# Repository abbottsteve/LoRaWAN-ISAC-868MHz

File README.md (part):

# 868 MHz LoRaWAN ISAC Surface-Permittivity Sensor Node (`Rev E.5`)

[-0A66C2?style=flat-square)](#1-motivation-status--system-specifications)

[-2E7D32?style=flat-square)](docs/firmware_and_pinmap.md)

An open-hardware Integrated Sensing and Communications (ISAC) sensor node operating in the European 863–870 MHz (EU868) band [6]. Rather than pairing an auxiliary microwave resonator with a separate telemetry radio, the board shares a single Inverted-F + Interdigital Evanescent-Field Antenna (`AE1`) and a single `STM32WLE5JC` / `SX1262` System-in-Package (`RAK3172LP-SIP-8-SM-NI`) across a low-loss (-0.80 dB) asymmetric return-loss bridge to measure near-field surface permittivity through a 0.80 mm radome and transmit Class A LoRaWAN uplinks over the same physical aperture.

| Front-Left Ray-Traced PCBA (90 × 40 mm) | Rear-Right RF Bridge & Sensing Aperture (`AE1`) |
| :---: | :---: |
|  |  |

### Documentation Navigation

| Document | Technical Scope |
| :--- | :--- |
| [**System Design Summary (6-Page PDF)**](docs/ISAC_868MHz_System_Design_and_Operation_Summary.pdf) | Printable A4 technical datasheet covering architecture, analytical signal model, benchmarks, CAD & references |
| [**RF Design, EM Solvers & Limitations**](docs/rf_design_and_simulation.md) | 2D-FVM CPWG cross-section, 2,000-trial bridge Monte-Carlo, 3D-FDTD plots, sensing boundary conditions & `Rev F.0` roadmap |
| [**Firmware, `U1` Pin Map & `FPort 10` Payload**](docs/firmware_and_pinmap.md) | Freestanding C11 execution flow, silicon errata, `RAK3172LP-SiP` LGA-73 pinout + overlay & 10-byte ChirpStack/TTN decoder |
| [**Turnkey BOM, Test Points & Enclosure**](docs/bom_and_enclosure.md) | Complete 46-line BOM, `TP1..TP5` probe map, self-draining ASA/PETG Option A/B blueprints & SWD provisioning CLI |
| [**Power Budget**](docs/power_budget.md) · [**Loaded Link Budget**](docs/rf_link_budget.md) | Split-rail LDO/switch current analysis (`STOP2` 2.85–3.25 µA) & wet-radome SF7/SF9/SF12 link-margin recovery |
| [**CST Studio Suite 3D Package**](cst_studio/README.md) | Parameterized SIMULIA CST Microwave Studio (`FIT` / curved `FEM`), Debye dispersion & Design Studio co-simulation |
| [**Pilot Bring-Up Checklist**](docs/bringup_report.md) · [**Open Items**](docs/OPEN_ITEMS.md) | First-article VNA correlation, 5–10 board pilot verification procedure & ETSI pre-compliance tracker |

---

## 1. Motivation, Status & System Specifications

Detecting glaze ice, water films, or hydrocarbon spills on remote outdoor assets—bridge decks, wind-turbine blades, roadways, and utility enclosures—typically forces a trade-off between optical/ultrasonic fouling and the cost/power overhead of standalone radar sensors. At UHF, the capacitive open end of a planar antenna exhibits strong resonant sensitivity to superstrate permittivity across a thin dielectric wall [1, 3, 4]. Inserting a -0.80 dB asymmetric return-loss bridge ahead of an interdigital-tip Inverted-F antenna lets the LoRa transceiver probe three brief +4.0 dBm CW tones across EU868 to classify surface loading before transmitting telemetry over LoRaWAN.

> **Hardware Status (`Rev E.5` — Pilot Batch in Fabrication):** Schematic, 2-layer PCB, 3D-FDTD and CST Studio models, freestanding C11 firmware, and the single-sided SMT archive ([`fab/ISAC_868_RevE5_PCBWay_Turnkey.zip`](fab/ISAC_868_RevE5_PCBWay_Turnkey.zip)) are frozen at `Rev E.5`. A 5–10 unit pilot batch is currently in turnkey assembly; all RF, sensitivity, and current figures reported here are simulation- and datasheet-derived predictions awaiting physical VNA and chamber correlation ([`docs/OPEN_ITEMS.md`](docs/OPEN_ITEMS.md)).

| Subsystem | `Rev E.5` Specification | Reference / Gate |
| :--- | :--- | :--- |
| **PCB & Finish** | 90.0 × 40.0 × 1.60 mm 2-layer FR-4 (1.51 mm core, $\varepsilon_r = 4.4 \pm 0.2$, 1 oz Cu), IPC-4552 ENIG, bare-ENIG `AE1` window, 0.10 mm top stencil | [`tools/check_dfm.py`](tools/check_dfm.py) |
| **Assembly Counts** | `92` footprints = `67` populated top SMD (`0` THT) + `10` DNP + `15` `BOARD_ONLY`; `131` tented 0.60/0.30 mm vias; 0 DRC / 0 ERC | [`docs/bom_and_enclosure.md`](docs/bom_and_enclosure.md) |
| **Radio / MCU (`U1`)** | `RAK3172LP-SIP-8-SM-NI` (`STM32WLE5JC` + `SX1262` `RFO_LP`, 3.0 V `DIO3` TCXO `0x06`, 15 µH wirewound SMPS); 15,948 B Flash / 408 B RAM | [`docs/firmware_and_pinmap.md`](docs/firmware_and_pinmap.md) |
| **CPWG & Bridge** | 51.90 Ω CPWG ($W = 1.08\text{ mm}, S = 0.28\text{ mm}$); `R1` = 8.2 Ω (`RT0402BRD078R2L`) asymmetric bridge ($C_{\text{par}} = 0.1305\text{ pF}$, IL = -0.802 dB, 50 Ω directivity = 24.81 dB) | [`docs/rf_design_and_simulation.md`](docs/rf_design_and_simulation.md) |
| **Detector (`U2`)** | Analog Devices `LT5538IDD#TRPBF` (19.0 mV/dB), TX-off Listen-Before-Sense blanking ($\le 320\text{ mV}$) & $\le 39.5\text{ mV}$ unpowered swing at +14 dBm TX | [`docs/rf_link_budget.md`](docs/rf_link_budget.md) |
| **Filter & `AE1`** | 3rd-order elliptic Pi-LPF ($2f_0 \ge 37.2\text{ dB}$, $3f_0 \ge 60.1\text{ dB}$); `AE1` bonded via 25 µm 3M 467MP to 0.80 mm ASA/PETG ($f_0 = 869.0\text{ MHz}$, $\eta_{\text{tot}} = 45.5$%, 43.73 MHz/RIU, 17.60 dB `P01` ice contrast) | [`rf/ifa_enclosure_mom.py`](rf/ifa_enclosure_mom.py) |
| **Power & Enclosure** | 1S LiPo or 3.6 V Li-SOCl<sub>2</sub> $\to$ `AO3401A` + 25 nA LDO (`U3`) + `VBAT`-gated `Q1` (2.85–3.25 µA `STOP2`); 95.7 × 45.7 × 16.1 mm open-East O-ring housing | [`docs/power_budget.md`](docs/power_budget.md) |

---

## 2. Operating Principle & Analytical Reflectometer Model

```mermaid
flowchart TB
    subgraph TXRX["U1: RAK3172LP-SiP (STM32WLE5JC + SX1262)"]
        direction LR
        MCU["Cortex-M4 @ 4 MHz<br/>12-bit SAR ADC + Flash NVM"]
        SYN["SX1262 RFO_LP (+4 dBm CW / +14 dBm LoRa)<br/>3.0 V DIO3 TCXO + Internal SPDT"]
    end

    subgraph RFF["50 Ω CPWG Spine, Return-Loss Bridge & Elliptic Filter"]
        direction LR
        CRF["C_RF (100 pF)<br/>DC Block"]
        BRG["Asymmetric Bridge (R1 = 8.2 Ω)<br/>IL = -0.80 dB | Dir = 24.8 dB"]
        ELL["3rd-Order Elliptic Pi-LPF<br/>2f0 ≥ 37.2 dB | 3f0 ≥ 60.1 dB"]
        AE1["AE1: Shared IFA + 5-Finger IDE<br/>25 µm 467MP + 0.80 mm ASA/PETG"]
        CRF --> BRG --> ELL --> AE1
    end

    subgraph DET["VBAT-Gated Logarithmic Reflectometer"]
        direction LR
        Q1["Q1: TPS22919 Load Switch<br/>VBAT → 3V3_DET (3.0 ms guard)"]
        LT["U2: LT5538IDD#TRPBF<br/>19.0 mV/dB | -88.8 dBm intercept"]
        LPF["RC Video LPF (1 kΩ, 100 nF)<br/>τ = 100 µs → TP4"]
        Q1 --> LT --> LPF
    end

    SYN --> CRF
    BRG -- "Coupled |Γ_in(f)|" --> LT
    MCU -- "PA8 (DET_EN)" --> Q1
    LPF -- "PA15 (ADC_IN11)" --> MCU
```

1. **Evanescent Fringing-Field Coupling:** The open end of `AE1` terminates in a 5-finger interdigital comb ($w = 1.30\text{ mm}$, $g = 1.20\text{ mm}$, $1/e$ penetration depth $\delta_E \approx (w + g)/\pi \approx 0.80\text{ mm}$ [1]) laminated directly to the 0.80 mm ASA/PETG window with 25 µm 3M 467MP acrylic adhesive. Superstrate media pull resonance downward from $f_0 = 869.0\text{ MHz}$ (Dry Air) to $776.0\text{ MHz}$ (Water [5]), reshaping the filter-cascaded reflection $\Gamma_{\text{in}}(f_k)$ across $f_1 = 863.1$, $f_2 = 866.5$, and $f_3 = 869.5\text{ MHz}$.
2. **3-Port Bridge Coupling & Ratiometric Detection:** Representing the bridge between `/BR_P` (Port 1), `/BR_Q` (Port 2, terminated in $\Gamma_{\text{in}}$), and `LT5538` `IN+` (Port 3) by its scattering matrix, the coupled RF power at tone $f_k$ ($k \in \{1, 2, 3\}$) is:

$$
P_{\text{det}}(f_k) = P_{\text{TX}} + 20\log_{10}\left\lvert S_{31}(f_k) + \frac{S_{21}(f_k)S_{32}(f_k)\thinspace\Gamma_{\text{in}}(f_k)}{1 - S_{22}(f_k)\thinspace\Gamma_{\text{in}}(f_k)}\right\rvert \quad [\text{dBm}] \qquad \text{(1)}
$$

`LT5538` maps $P_{\text{det}}(f_k)$ to a log-linear DC voltage ($K_{\text{det}} \approx 19.0\text{ mV/dB}$, log-intercept $P_0(T) \approx -88.8\text{ dBm}$), which firmware scales ratiometrically against the factory-calibrated internal bandgap ($V_{\text{REFINT,cal}}$ at 3.000 V, 16-sample oversampled sum $D_{\text{VREFINT}}$) so `VDDA` droop cancels:

$$
V(f_k) = K_{\text{det}}\left[P_{\text{det}}(f_k) - P_0(T)\right], \qquad V_{\text{DDA,true}} = 3000\text{ mV} \times \frac{16 \times V_{\text{REFINT,cal}}}{D_{\text{VREFINT}}} \qquad \text{(2)}
$$

Subtracting the Point-1 Dry-Air tare yields band-edge slope (`Tilt`, $\Delta L_{13}$), curvature (`Notch`, $\Delta N_2$), and calibrated mean reflection (`Level`, $\bar{L}$):

$$
\Delta L_{13} = \frac{V(f_1) - V(f_3)}{K_{\text{det}}} \qquad \text{(3)}
$$

$$
\Delta N_2 = \frac{\tfrac{1}{2}\left[V(f_1) + V(f_3)\right] - V(f_2)}{K_{\text{det}}} \qquad \text{(4)}
$$

$$
\bar{L} = \frac{P_{\text{det}}(f_1) + P_{\text{det}}(f_2) + P_{\text{det}}(f_3)}{3} \qquad \text{(5)}
$$

Because additive PA power offsets $\Delta P_{\text{TX}}$ and common-mode detector intercept drift $\Delta P_0(T)$ enter $V(f_1), V(f_2), V(f_3)$ identically across the 3.6 ms sweep, **both cancel analytically in (3) and (4)**, leaving only residual slope drift ($\approx 0.015\text{ dB/}^\circ\text{C}$) compensated on $\bar{L}$ in (5) via `ADC_IN12` die temperature and Point-2 (Al<sub>2</sub>O<sub>3</sub>) calibration.

---

## 3. Simulated 3-Tone Benchmarks & Physical Scope

> **Simulation Conditions:** +4.0 dBm CW sensing TX, $h_{\text{sup}} = 2.00\text{ mm}$ uniform superstrate on 0.80 mm ASA/PETG + 25 µm 467MP, 2-point calibrated (`VREFINT`/`TSEN` compensated; 3.30 V, 25 °C ADC codes). Both standalone $\lvert\Gamma_{\text{ant}}(f_2)\rvert$ at `AE1` Pad 1 and Pi-filter-cascaded $\lvert\Gamma_{\text{in}}(f_2)\rvert$ at `/BR_Q` ($f_2 = 866.5\text{ MHz}$) are listed; full `FPort = 10` byte encoding is in [`docs/firmware_and_pinmap.md`](docs/firmware_and_pinmap.md).

| Medium (2.0 mm) | $\varepsilon_r^*$ (868 MHz) | $f_0$ [MHz] | $\lvert\Gamma_{\text{ant}}(f_2)\rvert$ [dB] | $\lvert\Gamma_{\text{in}}(f_2)\rvert$ [dB] | $\eta_{\text{tot}}$ | ADC ($f_1/f_2/f_3$) | Tilt [dB] | Notch [dB] | Level [dBm] | SF | State (`FPort 10`) |
| :--- | :---: | :---: | :---: | :---: | :---: | :---: | :---: | :---: | :---: | :---: | :--- |
| **Dry Air** | $1.00 - j0.000$ | 869.0 | -23.69 | -20.83 | 45.5% | 1015/940/1096 | -3.44 | +4.88 | -45.66 | SF7 | `0=DRY_AIR` |
| **PTFE / Oil** | $2.10 - j0.0002$ | 849.0 | -7.04 | -7.14 | 35.4% | 1296/1307/1325 | -1.23 | +0.15 | -33.26 | SF7 | `1=OIL` |
| **Glaze Ice** | $3.20 - j0.003$ | 834.5 | -2.55 | -2.89 | 13.4% | 1419/1418/1419 | -0.01 | +0.06 | -28.63 | SF9 | `2=GLAZE_ICE` |
| **Alumina** (Al<sub>2</sub>O<sub>3</sub>) | $9.80 - j0.002$ | 783.0 | -0.36 | -0.53 | 5.1% | 1495/1476/1458 | +1.56 | +0.03 | -26.19 | SF12 | `3=IPA` (Cal) |
| **IPA** | $6.29 - j6.090$ | 794.0 | -1.63 | -2.19 | 4.8% | 1457/1439/1423 | +1.45 | +0.04 | -27.75 | SF12 | `3=IPA` |
| **Water Film** | $79.9 - j3.810$ | 776.0 | -0.46 | -0.72 | 9.6% | 1487/1472/1458 | +1.22 | +0.04 | -26.35 | SF12 | `4=LIQUID_WATER` |

**Figure 3.1 — Standalone `AE1` 3D-FDTD Return Loss $\lvert\Gamma_{\text{ant}}(f)\rvert$ and Filter-Cascaded Total Efficiency $\eta_{\text{tot}}(f)$:**

**Figure 3.2 — Self-Draining 0.80 mm ASA/PETG Enclosure, 3M 467MP Window & Parker ORD 5700 O-Ring Assembly:**

### Key Physical Boundary Conditions (Full Analysis in [`docs/rf_design_and_simulation.md`](docs/rf_design_and_simulation.md))
- **Thickness–Permittivity Degeneracy ($\varepsilon_r' \times h_{\text{film}}$):** Sub-millimeter condensation films ($h_{\text{sup}} < 0.3\text{ mm} \ll 2\delta_E$) partially load the fringing field and require +4.0 °C thermal gating plus multi-frame persistence in downstream analytics.
- **Narrowband EU868 Skirt Compression:** Above $\varepsilon_r' \ge 6$ ($f_0 < 800\text{ MHz}$), Water-vs-IPA separation relies on ~0.23 dB `Tilt` and ~1.4 dB calibrated `Level` on the upper skirt.
- **Counterpoise Mounting & Out-of-Band Selectivity:** Space the $0.145\lambda_0$ ground plane $\ge 10\text{–}15\text{ mm}$ off structural steel (or tare in-situ), and note that continuous RF jammers defer sweeps via `LBS` until an 868 MHz SAW pre-filter is added in `Rev F.0`.

---

## 4. Quick-Start Build & Verification

Prerequisites: `gcc`, `arm-none-eabi-gcc` (10.3+), and `python3` with KiCad 9 `pcbnew` bindings (for DFM/parity checks).

```bash
# 1. Build freestanding STM32WLE5JC firmware (.elf/.hex/.bin) & run 1,462 host HIL + NVM assertions
make -C firmware clean all

# 2. Run non-destructive KiCad DFM, Turnkey BOM/CPL, schematic-PCB consistency & doc parity gates
PYTHONDONTWRITEBYTECODE=1 python3 tools/rules_isac.py --verify
PYTHONDONTWRITEBYTECODE=1 python3 tools/check_dfm.py
PYTHONDONTWRITEBYTECODE=1 python3 tools/check_bom_cpl.py
PYTHONDONTWRITEBYTECODE=1 python3 tools/verify_design_consistency.py
PYTHONDONTWRITEBYTECODE=1 python3 tools/check_doc_parity.py

# 3. Verify CST Studio VBA macros, Touchstone de-embedding & 8 seeded manufacturing-defect traps
PYTHONDONTWRITEBYTECODE=1 python3 cst_studio/python/run_cst_batch.py --check-macros
PYTHONDONTWRITEBYTECODE=1 python3 cst_studio/python/postprocess_cst_results.py --verify-pipeline
PYTHONDONTWRITEBYTECODE=1 python3 tools/test_seeded_defects.py
```

SWD pogo-clip flashing and 2-point factory calibration commands (`tools/production_flash.sh`) are documented in [`docs/bom_and_enclosure.md`](docs/bom_and_enclosure.md) and [`docs/bringup_report.md`](docs/bringup_report.md).

---

## 5. Repository Structure

```text
├── ISAC_868_KiCad9.kicad_sch / .kicad_pcb / .kicad_pro / .kicad_dru   # Frozen Rev E.5 KiCad 9 schematic, PCB & DRC rules
├── ISAC.kicad_sym, ISAC.pretty/, 3dmodels/                            # Custom LGA-73, DFN-8, DNP & IFA+IDE libraries + STEP
├── firmware/                                                          # Freestanding C11 STM32WLE5JC ISAC + LoRaWAN 1.0.3 stack
├── rf/                                                                # 2D-FVM CPWG, 3D Yee-Grid FDTD & 2,000-trial bridge solvers
├── cst_studio/                                                        # SIMULIA CST Studio Suite 3D FIT/FEM & Debye co-sim package
├── enclosure/                                                         # Parametric flat-roof / open-East ASA/PETG enclosure & STLs
├── fab/                                                               # Frozen Rev E.5 PCBWay Turnkey archive & SHA256SUMS.txt
├── docs/                                                              # Modular engineering manuals, CAD sheets & datasheets
│   ├── ISAC_868MHz_System_Design_and_Operation_Summary.pdf / .md      # 6-page A4 printable design summary
│   ├── rf_design_and_simulation.md                                    # Deep EM solver results, bridge MC & sensing limitations
│   ├── firmware_and_pinmap.md                                         # C11 state machine, U1 LGA-73 pinout & FPort 10 wire contract
│   ├── bom_and_enclosure.md                                           # 46-line Turnkey BOM, TP1..TP5, Option A/B CAD & flashing CLI
│   └── power_budget.md, rf_link_budget.md, bringup_report.md, ...     # Rail/link budgets, pilot checklist, reports & datasheets
├── tools/                                                             # Parametric KiCad generators, DFM/parity gates & flasher
├── CITATION.cff                                                       # GitHub citation metadata (BibTeX / APA)
└── LICENSE                                                            # Apache License 2.0
```

---

## 6. Selected References, Citation & License

1. A. V. Mamishev, K. Sundara-Rajan, F. Yang, Y. Du, and M. Zahn, "Interdigital sensors and transducers," *Proceedings of the IEEE*, vol. 92, no. 5, pp. 808–845, May 2004, doi: [`10.1109/JPROC.2004.826603`](https://doi.org/10.1109/JPROC.2004.826603).
2. G. Marrocco, "The art of UHF RFID antenna design: Impedance-matching and size-reduction techniques," *IEEE Antennas and Propagation Magazine*, vol. 50, no. 1, pp. 66–79, Feb. 2008, doi: [`10.1109/MAP.2008.4494504`](https://doi.org/10.1109/MAP.2008.4494504).
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
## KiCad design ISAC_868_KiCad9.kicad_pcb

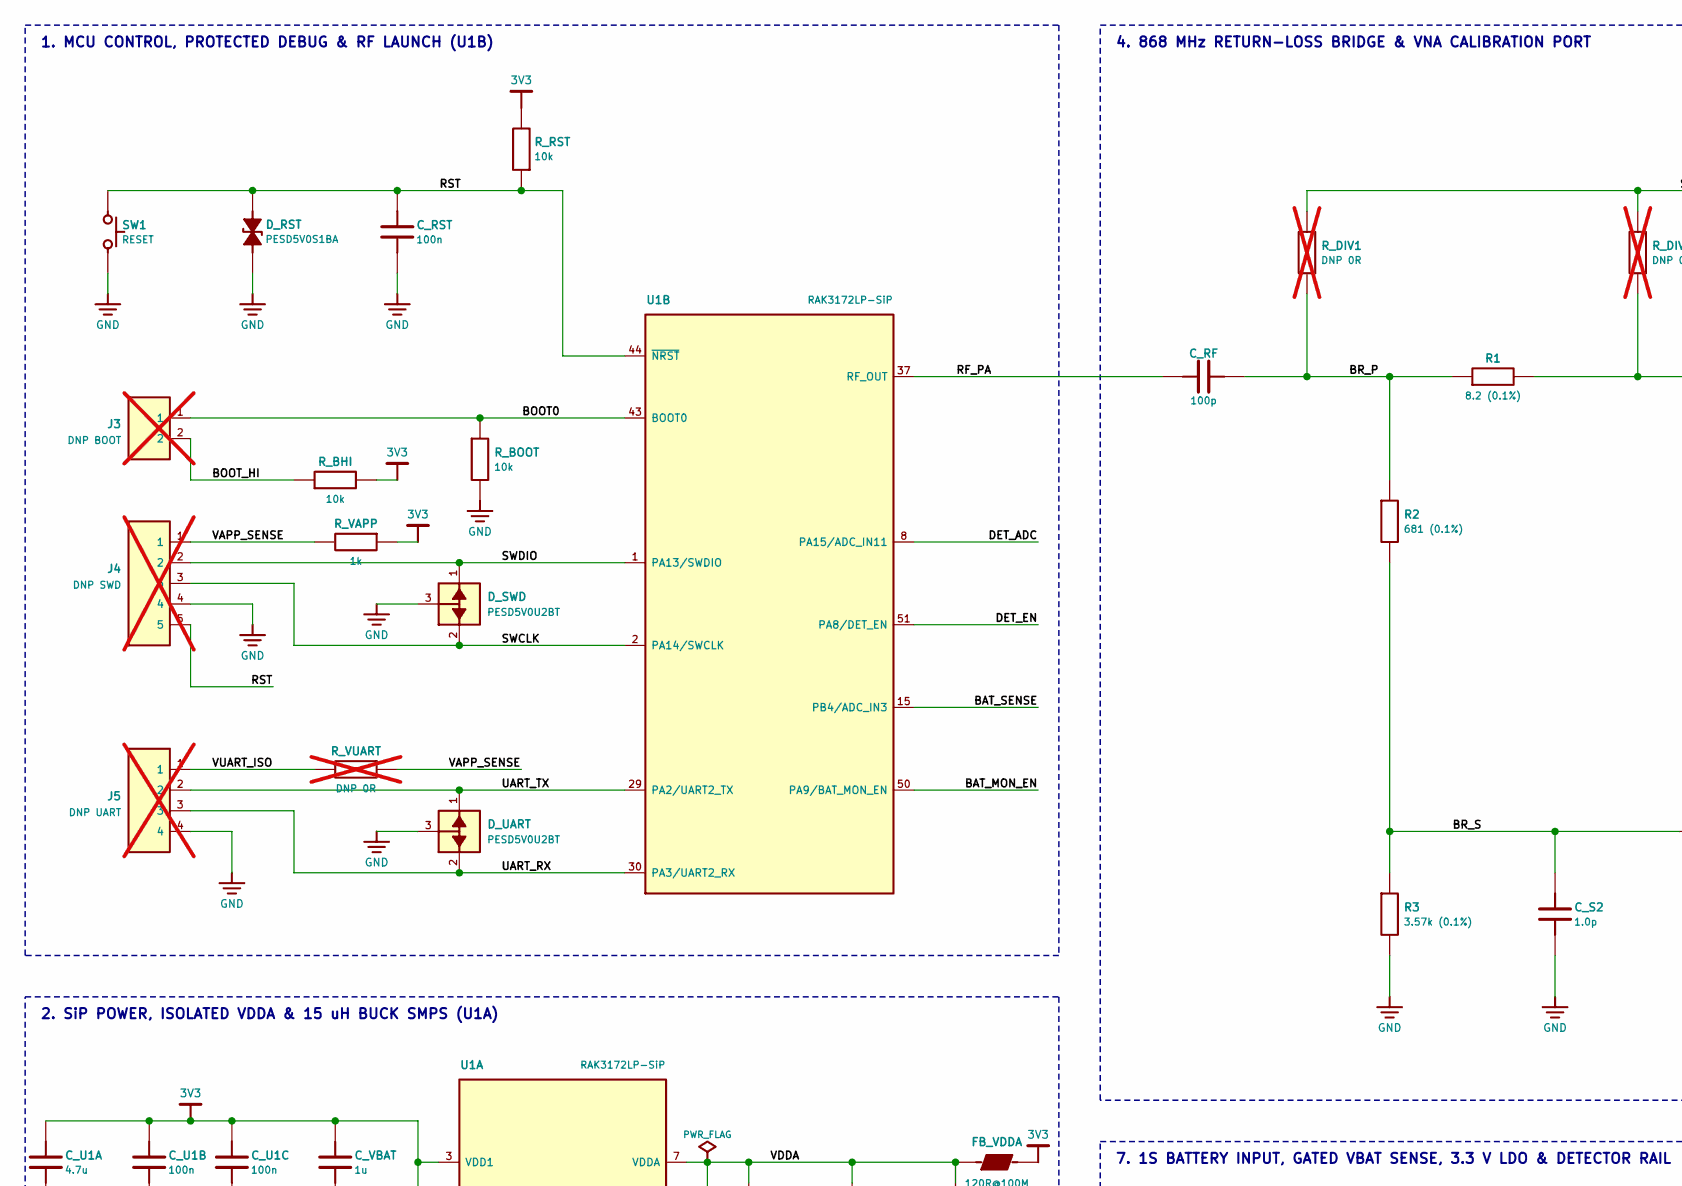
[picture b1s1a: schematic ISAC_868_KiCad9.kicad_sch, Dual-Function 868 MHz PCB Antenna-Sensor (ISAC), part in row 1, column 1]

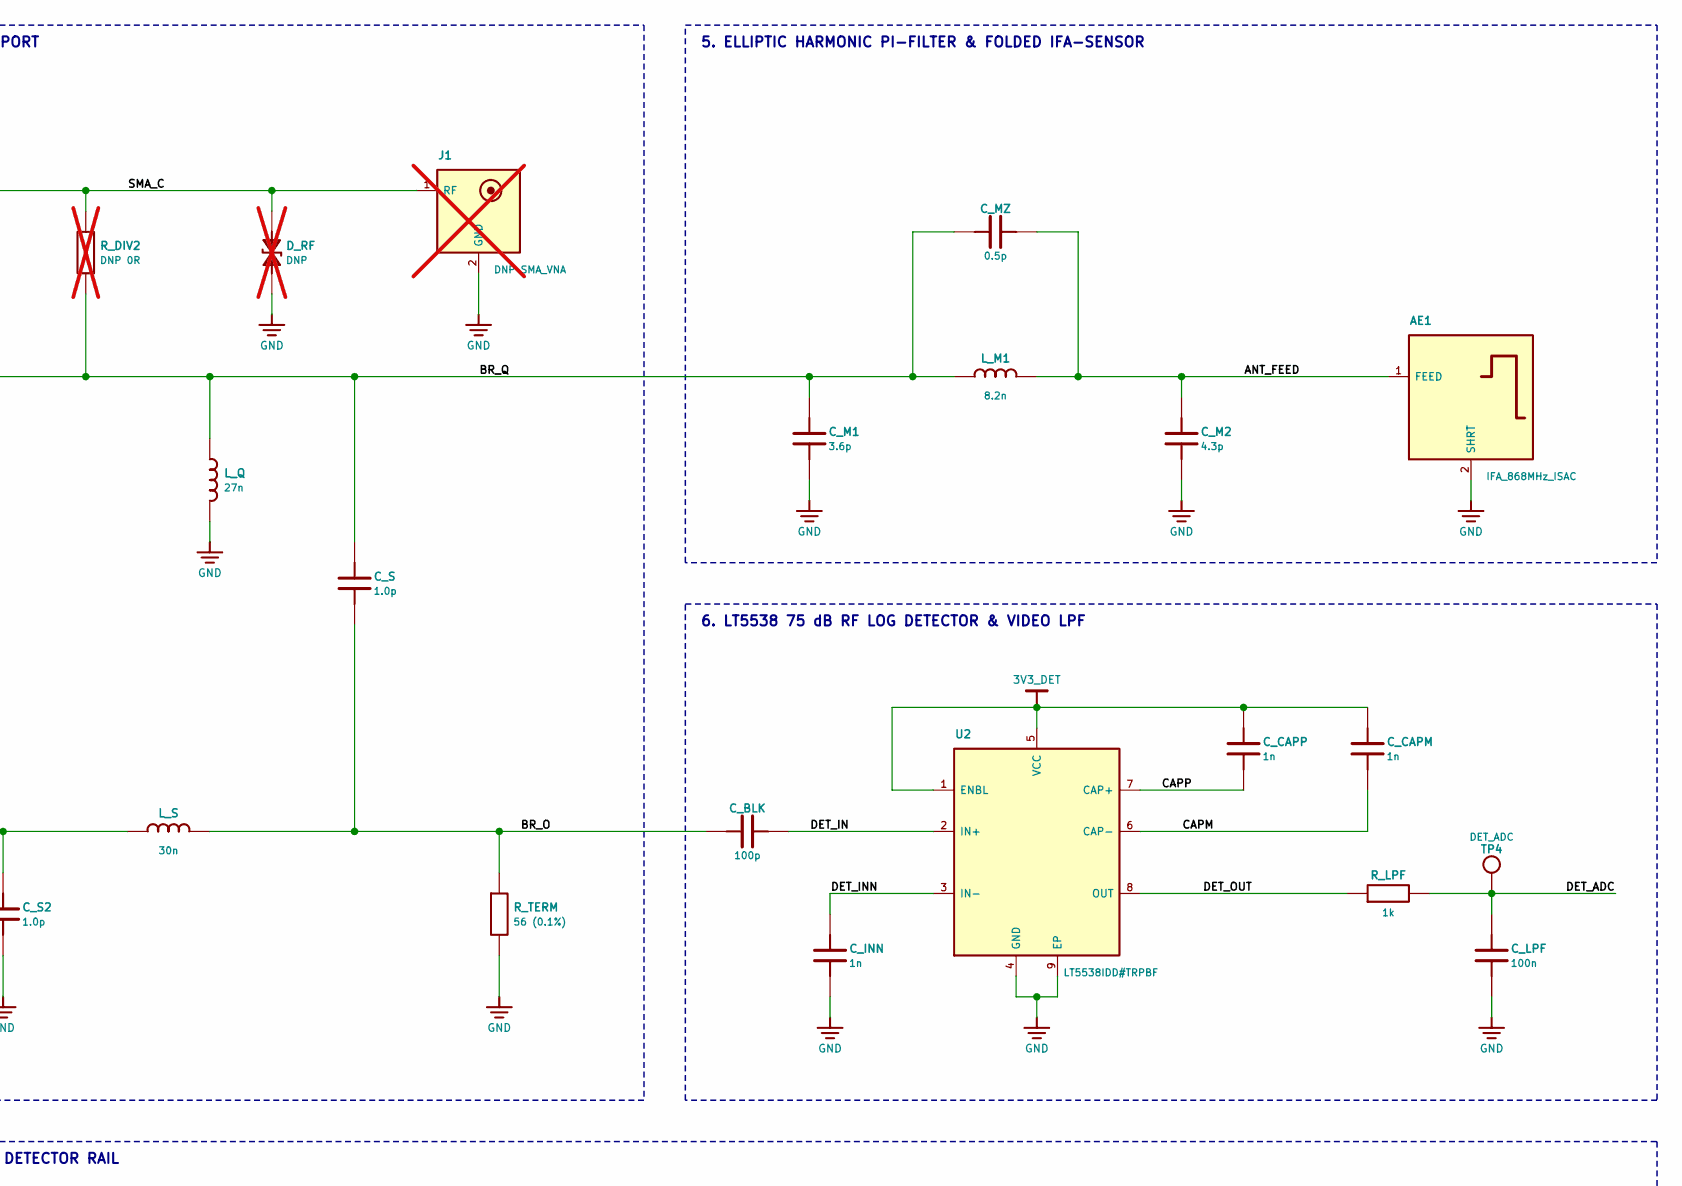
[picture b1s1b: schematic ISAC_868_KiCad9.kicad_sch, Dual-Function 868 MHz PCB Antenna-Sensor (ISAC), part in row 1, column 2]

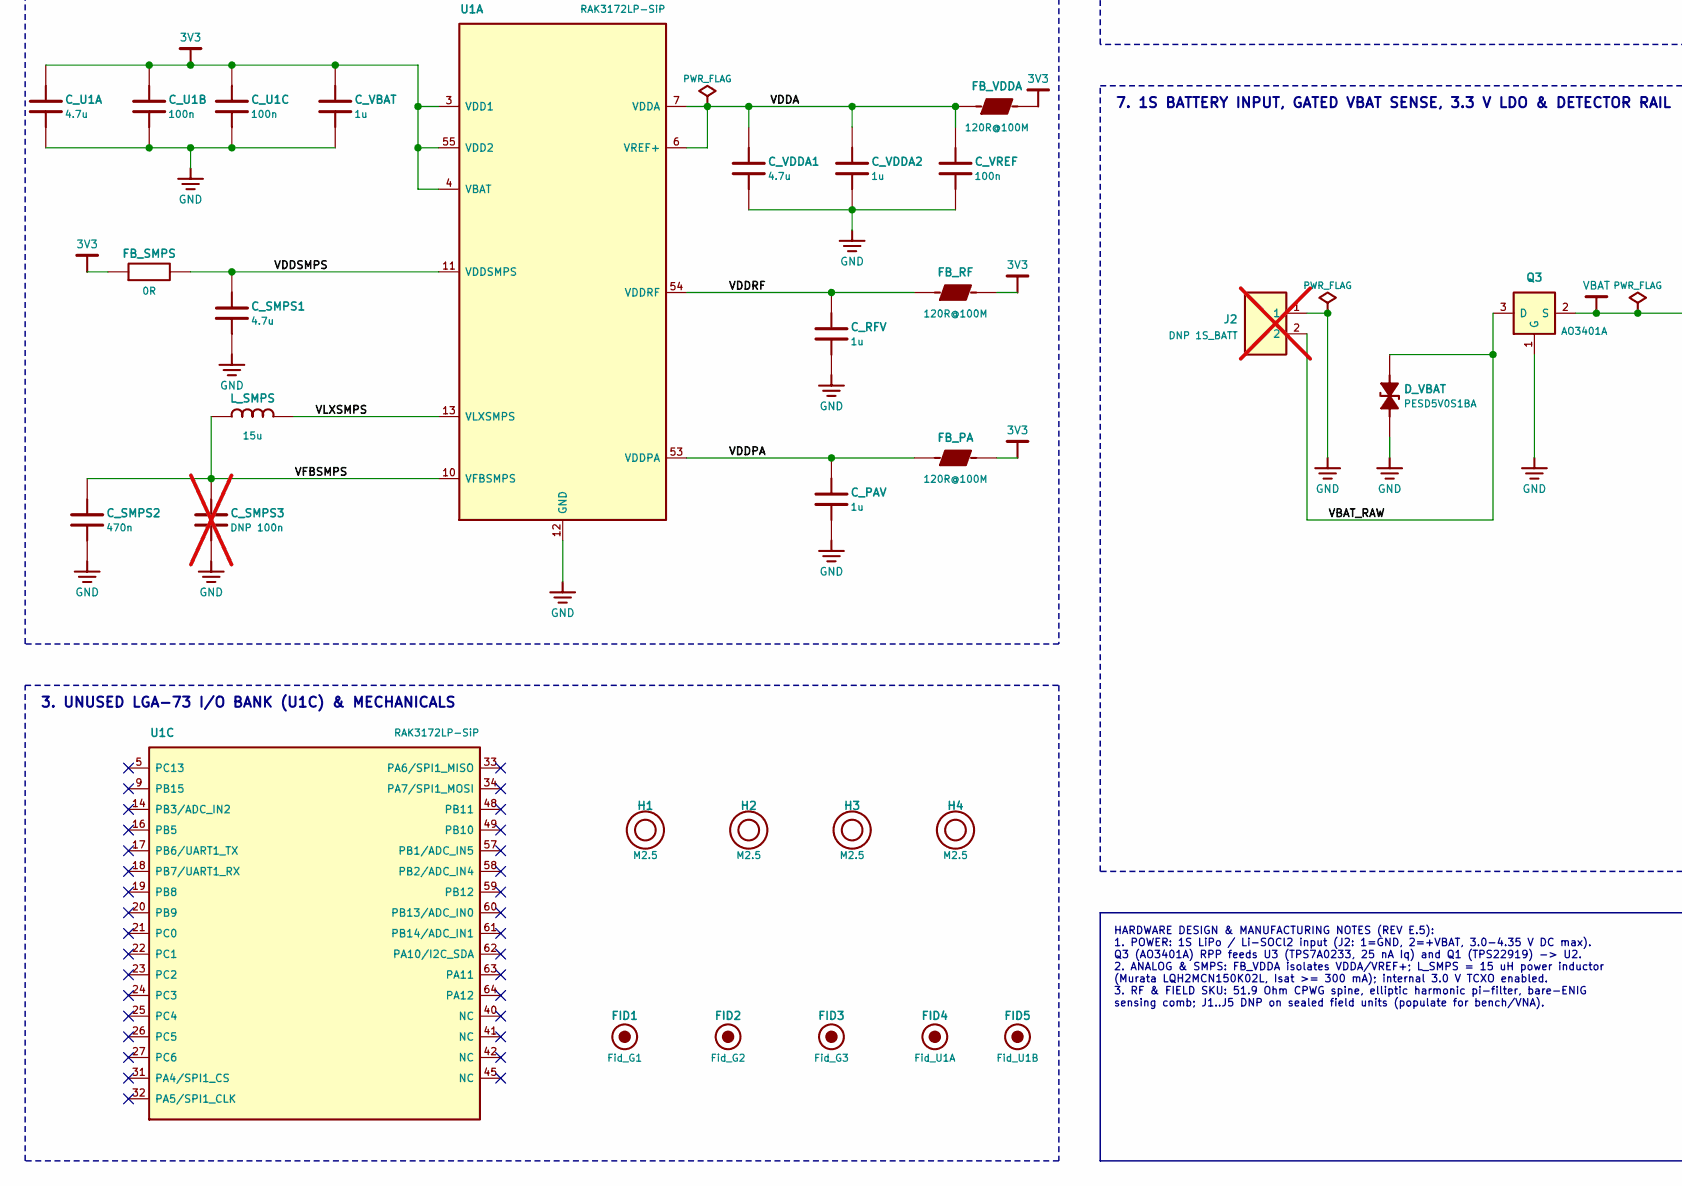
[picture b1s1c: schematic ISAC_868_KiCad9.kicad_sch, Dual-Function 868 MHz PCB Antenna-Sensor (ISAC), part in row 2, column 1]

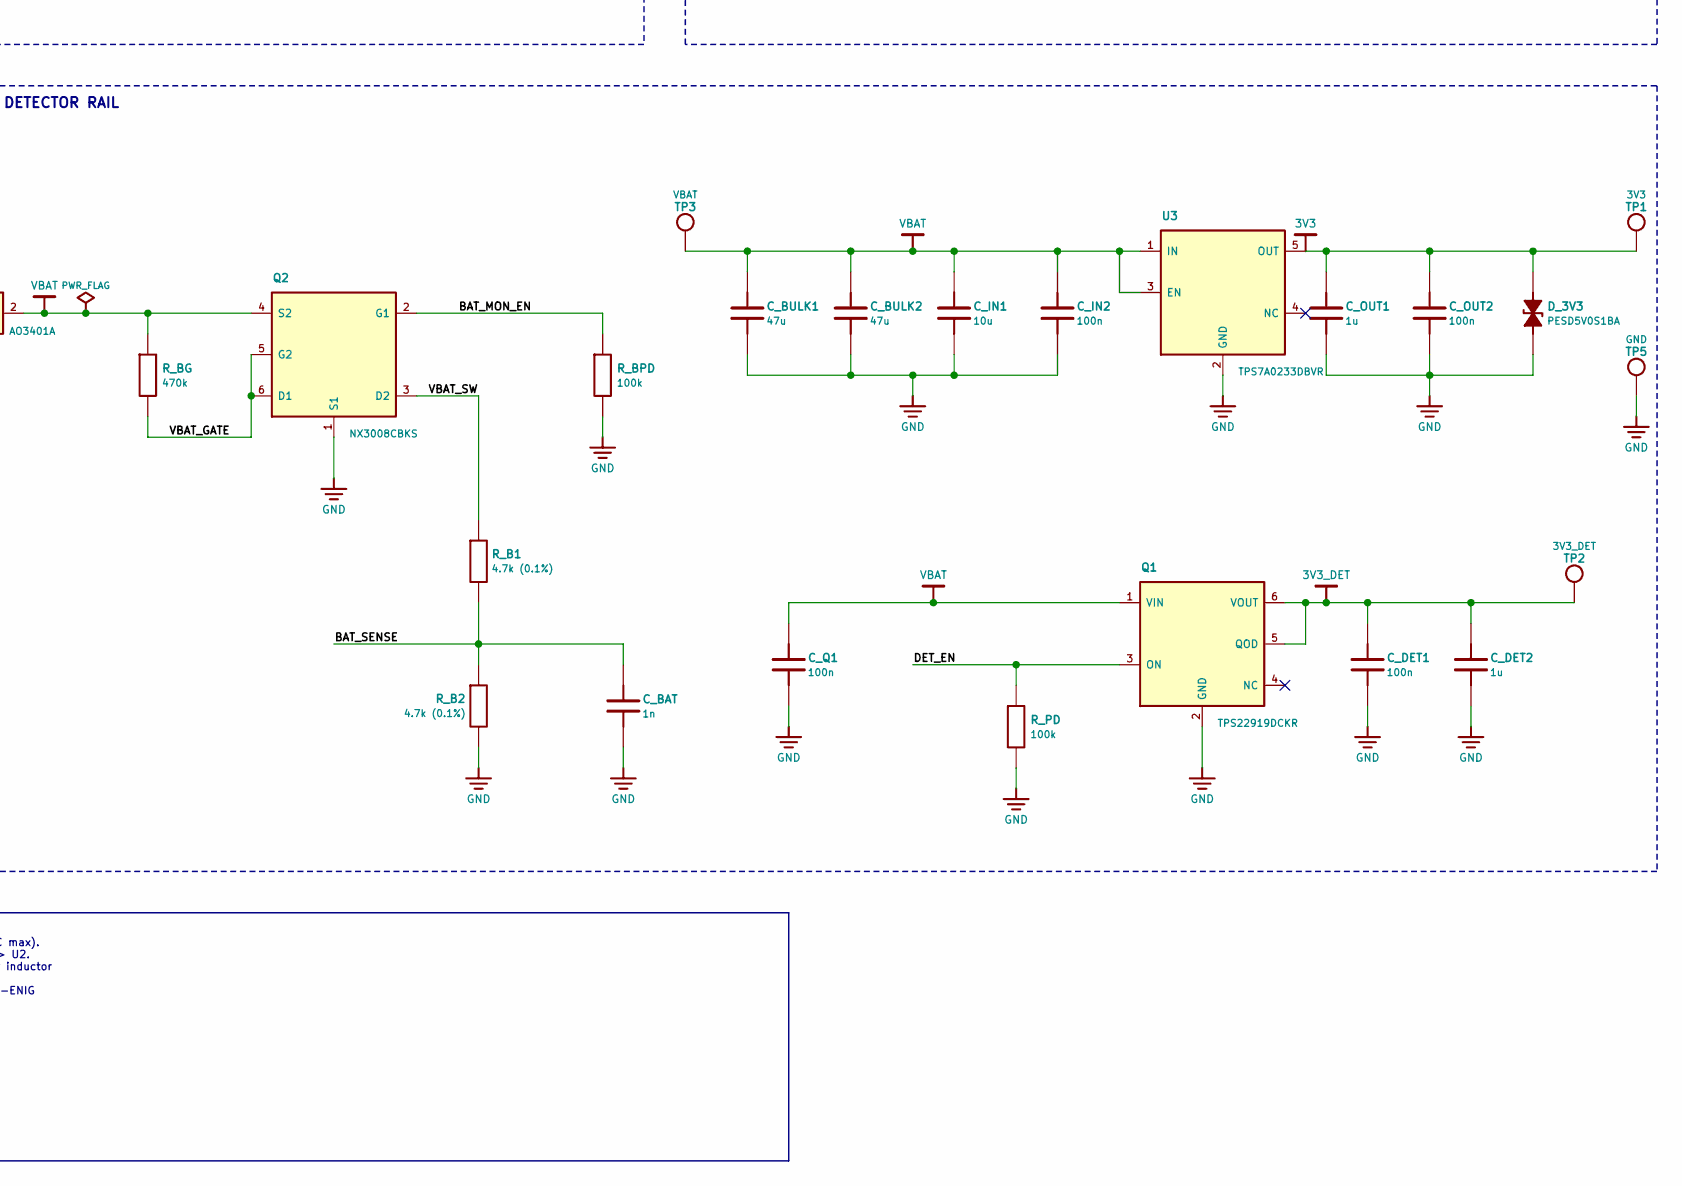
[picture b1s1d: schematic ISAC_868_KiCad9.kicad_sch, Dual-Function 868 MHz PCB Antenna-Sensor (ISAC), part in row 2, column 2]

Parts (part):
AE1: IFA_868MHz_ISAC; IFA_868MHz_ISAC_40x20mm; MPN PCB trace
C_BAT: 1n; C_0402_1005Metric; MPN GRM1555C1H102JA01D; LCSC C76947
C_BLK: 100p; C_0402_1005Metric; MPN GJM1555C1H101JB01D; LCSC Authorized: DigiKey/Mouser
C_BULK1, C_BULK2: 47u; C_0805_2012Metric; MPN GRM21BR61A476ME15L; LCSC C124129
C_CAPM: 1n; C_0402_1005Metric; MPN GRM1555C1H102JA01D; LCSC C76947
C_CAPP: 1n; C_0402_1005Metric; MPN GRM1555C1H102JA01D; LCSC C76947
C_DET1: 100n; C_0402_1005Metric; MPN GRM155R71C104KA88D; LCSC C71629
C_DET2: 1u; C_0603_1608Metric; MPN GRM188R71E105KA12D; LCSC C86020
C_IN1: 10u; C_0603_1608Metric; MPN GRM188R61E106MA73D; LCSC C91606
C_IN2: 100n; C_0402_1005Metric; MPN GRM155R71C104KA88D; LCSC C71629
C_INN: 1n; C_0402_1005Metric; MPN GRM1555C1H102JA01D; LCSC C76947
C_LPF: 100n; C_0402_1005Metric; MPN GRM155R71C104KA88D; LCSC C71629
C_M1: 3.6p; C_0402_1005Metric; MPN GJM1555C1H3R6WB01D; LCSC Authorized: DigiKey/Mouser
C_M2: 4.3p; C_0402_1005Metric; MPN GJM1555C1H4R3WB01D; LCSC Authorized: DigiKey/Mouser
C_MZ: 0.5p; C_0402_1005Metric; MPN GJM1555C1HR50WB01D; LCSC Authorized: DigiKey/Mouser
C_OUT1: 1u; C_0603_1608Metric; MPN GRM188R71E105KA12D; LCSC C86020
C_OUT2: 100n; C_0402_1005Metric; MPN GRM155R71C104KA88D; LCSC C71629
C_PAV: 1u; C_0402_1005Metric; MPN GRM155R61E105KA12D; LCSC C77009
C_Q1: 100n; C_0402_1005Metric; MPN GRM155R71C104KA88D; LCSC C71629
C_RF: 100p; C_0402_1005Metric; MPN GJM1555C1H101JB01D; LCSC Authorized: DigiKey/Mouser
C_RFV: 1u; C_0402_1005Metric; MPN GRM155R61E105KA12D; LCSC C77009
C_RST: 100n; C_0402_1005Metric; MPN GRM155R71C104KA88D; LCSC C71629
C_S, C_S2: 1.0p; C_0402_1005Metric; MPN GJM1555C1H1R0WB01D; LCSC C161339
C_SMPS1: 4.7u; C_0402_1005Metric; MPN GRM155R61A475MEAAD; LCSC C335105
C_SMPS2: 470n; C_0402_1005Metric; MPN GRM155R71C474KA01D; LCSC C52923
C_SMPS3: DNP 100n; C_0402_1005Metric_DNP_NoPaste; MPN GRM155R71C104KA88D; LCSC C71629; not fitted
C_U1A: 4.7u; C_0603_1608Metric; MPN GRM188R61E475KE11D; LCSC C90057
C_U1B, C_U1C: 100n; C_0402_1005Metric; MPN GRM155R71C104KA88D; LCSC C71629
C_VBAT: 1u; C_0402_1005Metric; MPN GRM155R61E105KA12D; LCSC C77009
C_VDDA1: 4.7u; C_0603_1608Metric; MPN GRM188R61E475KE11D; LCSC C90057
C_VDDA2: 1u; C_0402_1005Metric; MPN GRM155R61E105KA12D; LCSC C77009
C_VREF: 100n; C_0402_1005Metric; MPN GRM155R71C104KA88D; LCSC C71629
D_3V3: PESD5V0S1BA; D_SOD-323; MPN PESD5V0S1BA,115; LCSC C19224
D_RF: DNP; D_SOD-523_DNP_NoPaste; MPN ESD9B5.0ST5G; LCSC Authorized: DigiKey/Mouser; not fitted
D_RST: PESD5V0S1BA; D_SOD-323; MPN PESD5V0S1BA,115; LCSC C19224
D_SWD: PESD5V0U2BT; SOT-23; MPN PESD5V0U2BT,215; LCSC Authorized: DigiKey/Mouser
D_UART: PESD5V0U2BT; SOT-23; MPN PESD5V0U2BT,215; LCSC Authorized: DigiKey/Mouser
D_VBAT: PESD5V0S1BA; D_SOD-323; MPN PESD5V0S1BA,115; LCSC C19224
FB_PA: 120R@100M; L_0402_1005Metric; MPN BLM15AG121SN1D; LCSC C85812
FB_RF: 120R@100M; L_0402_1005Metric; MPN BLM15AG121SN1D; LCSC C85812
FB_SMPS: 0R; R_0402_1005Metric; MPN RC0402JR-070RL; LCSC C60485
FB_VDDA: 120R@100M; L_0402_1005Metric; MPN BLM15AG121SN1D; LCSC C85812
FID1: Fid_G1; Fiducial_1mm_Mask2mm
FID2: Fid_G2; Fiducial_1mm_Mask2mm
FID3: Fid_G3; Fiducial_1mm_Mask2mm
FID4: Fid_U1A; Fiducial_1mm_Mask2mm
FID5: Fid_U1B; Fiducial_1mm_Mask2mm
H1, H2, H3, H4: M2.5; MountingHole_2.7mm_M2.5
J1: DNP SMA_VNA; SMA_Molex_73251-1153_EdgeMount_Horizontal_HandSolder; MPN 73251-1153; LCSC Authorized: Mouser/DigiKey; not fitted
J2: DNP 1S_BATT; JST_PH_B2B-PH-K_1x02_P2.00mm_Vertical; MPN B2B-PH-K-S; LCSC C131337; not fitted
J3: DNP BOOT; PinHeader_1x02_P2.54mm_Vertical; MPN PZ254V-11-02P; LCSC C492401; not fitted
J4: DNP SWD; PinHeader_1x05_P2.54mm_Vertical; MPN PZ254V-11-05P; LCSC C492404; not fitted
J5: DNP UART; PinHeader_1x04_P2.54mm_Vertical; MPN PZ254V-11-04P; LCSC C492403; not fitted
L_M1: 8.2n; L_0402_1005Metric; MPN LQW15AN8N2G00D; LCSC Authorized: DigiKey/Mouser
L_Q: 27n; L_0402_1005Metric; MPN LQW15AN27NG00D; LCSC Authorized: DigiKey/Mouser
L_S: 30n; L_0402_1005Metric; MPN LQW15AN30NG00D; LCSC Authorized: DigiKey/Mouser
L_SMPS: 15u; L_0805_2012Metric; MPN LQH2MCN150K02L; LCSC C86089
Q1: TPS22919DCKR; SOT-363_SC-70-6; MPN TPS22919DCKR; LCSC Authorized: DigiKey/Mouser
Q2: NX3008CBKS; SOT-363_SC-70-6; MPN NX3008CBKS,115; LCSC C456076
Q3: AO3401A; SOT-23; MPN AO3401A; LCSC C15127
R1: 8.2 (0.1%); R_0402_1005Metric; MPN RT0402BRD078R2L; LCSC Authorized: DigiKey/Mouser
R2: 681 (0.1%); R_0402_1005Metric; MPN RG1005P-6810-B-T5; LCSC Authorized: DigiKey/Mouser
R3: 3.57k (0.1%); R_0402_1005Metric; MPN RG1005P-3571-B-T5; LCSC Authorized: DigiKey/Mouser
R_B1, R_B2: 4.7k (0.1%); R_0402_1005Metric; MPN RG1005P-472-B-T5; LCSC Authorized: DigiKey/Mouser
R_BG: 470k; R_0402_1005Metric; MPN RC0402FR-07470KL; LCSC C482181
R_BHI: 10k; R_0402_1005Metric; MPN RC0402FR-0710KL; LCSC C60490
R_BOOT: 10k; R_0402_1005Metric; MPN RC0402FR-0710KL; LCSC C60490
R_BPD: 100k; R_0402_1005Metric; MPN RC0402FR-07100KL; LCSC C60491
R_DIV1, R_DIV2: DNP 0R; R_0402_1005Metric_DNP_NoPaste; MPN RC0402JR-070RL; LCSC C60485; not fitted
R_LPF: 1k; R_0402_1005Metric; MPN RC0402FR-071KL; LCSC C106235
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
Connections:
3V3: C_OUT1.1, C_OUT2.1, C_U1A.1, C_U1B.1, C_U1C.1, C_VBAT.1, D_3V3.1, FB_PA.2, FB_RF.2, FB_SMPS.1, FB_VDDA.2, R_BHI.2, R_RST.2, R_VAPP.1, TP1.1, U1.3 (VDD1), U1.4 (VBAT), U1.55 (VDD2), U3.5 (OUT)
3V3_DET: C_CAPM.2, C_CAPP.2, C_DET1.1, C_DET2.1, Q1.5 (QOD), Q1.6 (VOUT), TP2.1, U2.1 (ENBL), U2.5 (VCC)
/ANT_FEED: AE1.1 (FEED), C_M2.1, C_MZ.2, L_M1.2
/BAT_MON_EN: Q2.2 (G1), R_BPD.1, U1.50 (PA9/BAT_MON_EN)
/BAT_SENSE: C_BAT.1, R_B1.2, R_B2.1, U1.15 (PB4/ADC_IN3)
/BOOT0: J3.1, R_BOOT.1, U1.43 (BOOT0)
/BOOT_HI: J3.2, R_BHI.1
/BR_O: C_BLK.1, C_S.2, L_S.2, R_TERM.1
/BR_P: C_RF.2, R1.1, R2.1, R_DIV1.1
/BR_Q: C_M1.1, C_MZ.1, C_S.1, L_M1.1, L_Q.1, R1.2, R_DIV2.1
/BR_S: C_S2.1, L_S.1, R2.2, R3.1
/CAPM: C_CAPM.1, U2.6 (CAP-)
/CAPP: C_CAPP.1, U2.7 (CAP+)
/DET_ADC: C_LPF.1, R_LPF.2, TP4.1, U1.8 (PA15/ADC_IN11)
/DET_EN: Q1.3 (ON), R_PD.1, U1.51 (PA8/DET_EN)
/DET_IN: C_BLK.2, U2.2 (IN+)
/DET_INN: C_INN.1, U2.3 (IN-)
/DET_OUT: R_LPF.1, U2.8 (OUT)
/RF_PA: C_RF.1, U1.37 (RF_OUT)
/RST: C_RST.1, D_RST.1, J4.5, R_RST.1, SW1.1, U1.44 (~NRST)
/SMA_C: D_RF.1, J1.1 (RF), R_DIV1.2, R_DIV2.2
/SWCLK: D_SWD.2 (IO2), J4.3, U1.2 (PA14/SWCLK)
/SWDIO: D_SWD.1 (IO1), J4.2, U1.1 (PA13/SWDIO)
/UART_RX: D_UART.2 (IO2), J5.3, U1.30 (PA3/UART2_RX)
/UART_TX: D_UART.1 (IO1), J5.2, U1.29 (PA2/UART2_TX)
/VAPP_SENSE: J4.1, R_VAPP.2, R_VUART.1
/VBAT_GATE: Q2.5 (G2), Q2.6 (D1), R_BG.2
/VBAT_RAW: D_VBAT.1, J2.2, Q3.3 (D)
/VBAT_SW: Q2.3 (D2), R_B1.1
/VDDA: C_VDDA1.1, C_VDDA2.1, C_VREF.1, FB_VDDA.1, U1.6 (VREF+), U1.7 (VDDA)
/VDDPA: C_PAV.1, FB_PA.1, U1.53 (VDDPA)
/VDDRF: C_RFV.1, FB_RF.1, U1.54 (VDDRF)
/VDDSMPS: C_SMPS1.1, FB_SMPS.2, U1.11 (VDDSMPS)
/VFBSMPS: C_SMPS2.1, C_SMPS3.1, L_SMPS.1, U1.10 (VFBSMPS)
/VLXSMPS: L_SMPS.2, U1.13 (VLXSMPS)
/VUART_ISO: J5.1, R_VUART.2
GND: AE1.2 (SHRT), C_BAT.2, C_BULK1.2, C_BULK2.2, C_DET1.2, C_DET2.2, C_IN1.2, C_IN2.2, C_INN.2, C_LPF.2, C_M1.2, C_M2.2, C_OUT1.2, C_OUT2.2, C_PAV.2, C_Q1.2, C_RFV.2, C_RST.2, C_S2.2, C_SMPS1.2, C_SMPS2.2, C_SMPS3.2, C_U1A.2, C_U1B.2, C_U1C.2, C_VBAT.2, C_VDDA1.2, C_VDDA2.2, C_VREF.2, D_3V3.2, D_RF.2, D_RST.2, D_SWD.3 (GND), D_UART.3 (GND), D_VBAT.2, J1.2 (GND), J2.1, J4.4, J5.4, L_Q.2, Q1.2 (GND), Q2.1 (S1), Q3.1 (G), R3.2, R_B2.2, R_BOOT.2, R_BPD.2, R_PD.2, R_TERM.2, SW1.2, TP5.1, U1.12 (GND), U1.28 (GND), U1.35 (GND), U1.36 (GND), U1.38 (GND), U1.39 (GND), U1.46 (GND), U1.47 (GND), U1.52 (GND), U1.56 (GND), U1.65 (GND), U1.66 (GND), U1.67 (GND), U1.68 (GND), U1.69 (GND), U1.70 (GND), U1.71 (GND), U1.72 (GND), U1.73 (GND), U2.4 (GND), U2.9 (EP), U3.2 (GND)
VBAT: C_BULK1.1, C_BULK2.1, C_IN1.1, C_IN2.1, C_Q1.1, Q1.1 (VIN), Q2.4 (S2), Q3.2 (S), R_BG.1, TP3.1, U3.1 (IN), U3.3 (EN)

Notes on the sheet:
1. MCU CONTROL, PROTECTED DEBUG & RF LAUNCH (U1B)
2. SiP POWER, ISOLATED VDDA & 15 uH BUCK SMPS (U1A)
3. UNUSED LGA-73 I/O BANK (U1C) & MECHANICALS
4. 868 MHz RETURN-LOSS BRIDGE & VNA CALIBRATION PORT
5. ELLIPTIC HARMONIC PI-FILTER & FOLDED IFA-SENSOR
6. LT5538 75 dB RF LOG DETECTOR & VIDEO LPF
7. 1S BATTERY INPUT, GATED VBAT SENSE, 3.3 V LDO & DETECTOR RAIL
HARDWARE DESIGN & MANUFACTURING NOTES (REV E.5): 1. POWER: 1S LiPo / Li-SOCl2 input (J2: 1=GND, 2=+VBAT, 3.0-4.35 V DC max). Q3 (AO3401A) RPP feeds U3 (TPS7A0233, 25 nA Iq) and Q1 (TPS22919) -> U2. 2. ANALOG & SMPS: FB_VDDA isolates VDDA/VREF+; L_SMPS = 15 uH power inductor (Murata LQH2MCN150K02L, 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

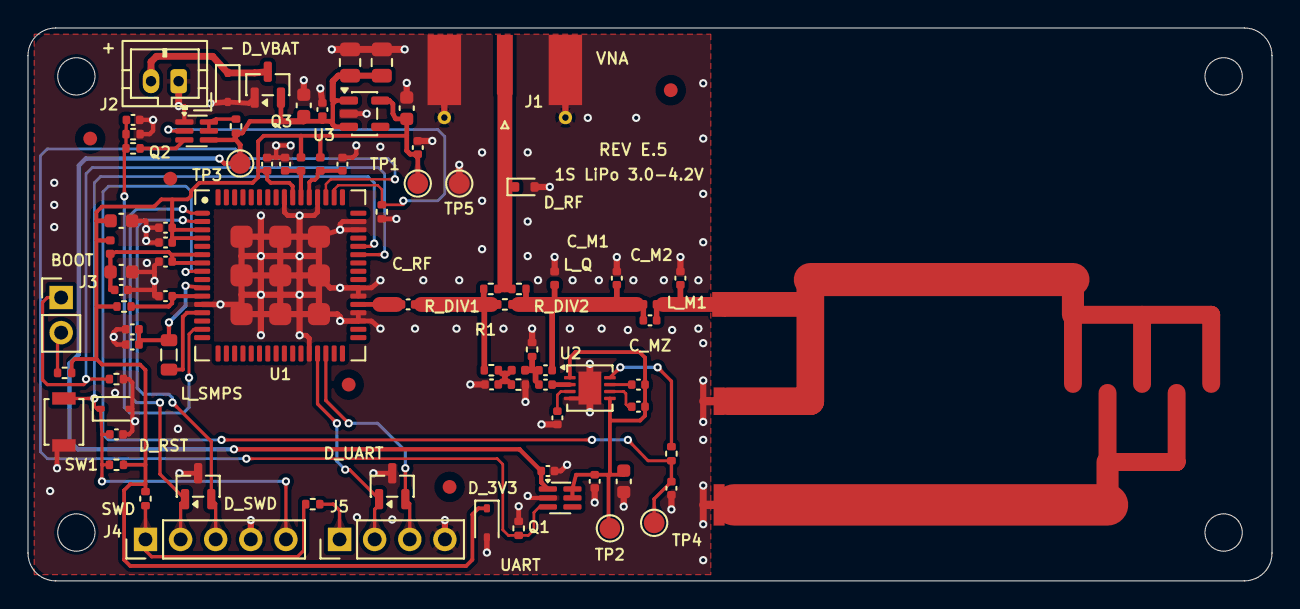
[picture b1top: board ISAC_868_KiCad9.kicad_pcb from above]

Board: 2 copper layers, 90.0 x 40.0 mm, 92 parts (0 on the bottom side), 38 nets.

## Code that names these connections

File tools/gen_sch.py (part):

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  * Ultra-low-sleep (< 2.5 uA typ across VBAT = 3.0..4.2 V):
    - U3 TI TPS7A0233DBVR (SOT-23-5: 1=IN, 2=GND, 3=EN, 4=NC, 5=OUT;
      Iq = 25 nA typ, 200 mA continuous) + Q3 AO3401A ideal diode.
    - Independent PA9 (BAT_MON_EN) high-side gated battery divider via Q2
      (Nexperia NX3008CBKS,115 complementary +/-30 V N+P MOSFET, SOT-363) +
      R_BG (470k) + R_B1/R_B2 (4.7k 0.1%) + C_BAT (1n 50V C0G): 0 nA sleep bleed.
    - Header LiPo back-feed isolation: R_VAPP (1k) on J4.1 VAPP_SENSE,
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    box_pin("L", u1a_hw, u1a_hh, 55, "VDD2", "power_in", 6, unit=1),
    box_pin("L", u1a_hw, u1a_hh, 4, "VBAT", "power_in", 4, unit=1),
    box_pin("L", u1a_hw, u1a_hh, 11, "VDDSMPS", "passive", 0, unit=1),
    box_pin("L", u1a_hw, u1a_hh, 13, "VLXSMPS", "passive", -7, unit=1),
    box_pin("L", u1a_hw, u1a_hh, 10, "VFBSMPS", "passive", -10, unit=1),

    box_pin("R", u1a_hw, u1a_hh, 7, "VDDA", "power_in", 8, unit=1),
    box_pin("R", u1a_hw, u1a_hh, 6, "VREF+", "power_in", 6, unit=1),
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u1b_pins = [
    box_pin("L", u1b_hw, u1b_hh, 44, "~{NRST}", "input", 12, unit=2),
    box_pin("L", u1b_hw, u1b_hh, 43, "BOOT0", "input", 9, unit=2),
    box_pin("L", u1b_hw, u1b_hh, 1, "PA13/SWDIO", "bidirectional", 2, unit=2),
    box_pin("L", u1b_hw, u1b_hh, 2, "PA14/SWCLK", "bidirectional", -2, unit=2),
    box_pin("L", u1b_hw, u1b_hh, 29, "PA2/UART2_TX", "output", -9, unit=2),
    box_pin("L", u1b_hw, u1b_hh, 30, "PA3/UART2_RX", "input", -13, unit=2),

    box_pin("R", u1b_hw, u1b_hh, 37, "RF_OUT", "bidirectional", 11, unit=2),
    box_pin("R", u1b_hw, u1b_hh, 8, "PA15/ADC_IN11", "input", 3, unit=2),
    box_pin("R", u1b_hw, u1b_hh, 51, "PA8/DET_EN", "output", -1, unit=2),
    box_pin("R", u1b_hw, u1b_hh, 15, "PB4/ADC_IN3", "input", -5, unit=2),
    box_pin("R", u1b_hw, u1b_hh, 50, "PA9/BAT_MON_EN", "output", -9, unit=2),
]

# Unit 3 (U1C): Unused LGA-73 GPIO & Internal NC Termination Bank (33 pins)
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    net_label("BOOT0", 29, 24)
    add_pwr("GND", *pin_grid("R_BOOT", 2))
    chain(pin_grid("J3", 2), (13, 27), pin_grid("R_BHI", 1))
    net_label("BOOT_HI", 14, 27)
    chain(pin_grid("R_BHI", 2), (23, 27))
    add_pwr("3V3", 23, 27)

    # J4 SWD+NRST header + R_VAPP + D_SWD feed-through -> U1B SWDIO (34,31) & SWCLK (34,35)
    chain(pin_grid("J4", 1), pin_grid("R_VAPP", 2))
    net_label("VAPP_SENSE", 14, 30)
    chain(pin_grid("R_VAPP", 1), (24, 30))
    add_pwr("3V3", 24, 30)

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
    # J5 UART2 header + R_VUART + D_UART feed-through -> U1B UART_TX (34,42) & UART_RX (34,46)
    chain(pin_grid("J5", 1), pin_grid("R_VUART", 2))
    net_label("VUART_ISO", 14, 41)
    chain(pin_grid("R_VUART", 1), (29, 41))
    net_label("VAPP_SENSE", 29, 41, just="right")

    chain(pin_grid("J5", 2), pin_grid("U1", 29))
    net_label("UART_TX", 28, 42)
    chain(pin_grid("J5", 3), (18, 43), (18, 46), pin_grid("U1", 30))
    net_label("UART_RX", 28, 46)
    chain(pin_grid("D_UART", 3), (22, 44))
    add_pwr("GND", 22, 44)
    chain(pin_grid("J5", 4), (15, 44), (15, 46))
    add_pwr("GND", 15, 46)

    # U1B Right-hand Sensing & Power Control stubs (terminated at net_label endpoints)
    for _upin, _ulbl in ((8, "DET_ADC"), (51, "DET_EN"), (15, "BAT_SENSE"), (50, "BAT_MON_EN")):
        px, py = pin_grid("U1", _upin)
        chain((px, py), (54, py))
        net_label(_ulbl, 54, py, just="right")
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    add_pwr("GND", *pin_grid("C_SMPS1", 2))

    chain(pin_grid("L_SMPS", 2), pin_grid("U1", 13))
    net_label("VLXSMPS", 19, 75)
    chain(pin_grid("L_SMPS", 1), (14, 78))
    chain((8, 78), pin_grid("U1", 10))
    chain((8, 78), pin_grid("C_SMPS2", 1))
    chain((14, 78), pin_grid("C_SMPS3", 1))
    net_label("VFBSMPS", 18, 78)
    add_pwr("GND", 8, 82)
    add_pwr("GND", 14, 82)

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    # 4. 868 MHz Return-Loss Bridge & VNA Calibration Port
    # ======================================================================
    chain(pin_grid("U1", 37), pin_grid("C_RF", 1))
    net_label("RF_PA", 50, 22)
    chain(pin_grid("C_RF", 2), pin_grid("R1", 1))
    net_label("BR_P", 69, 22)

    chain((67, 22), pin_grid("R_DIV1", 1))
    chain((83, 22), pin_grid("R_DIV2", 1))
    chain(pin_grid("R_DIV1", 2), (67, 13), pin_grid("J1", 1))
    chain(pin_grid("R_DIV2", 2), (83, 13))
    chain((92, 13), pin_grid("D_RF", 1))
    net_label("SMA_C", 85, 13)
    chain(pin_grid("D_RF", 2), (92, 19))
    add_pwr("GND", 92, 19)
    chain(pin_grid("J1", 2), (102, 19))
    add_pwr("GND", 102, 19)

    chain(pin_grid("R1", 2), pin_grid("L_M1", 1))
    net_label("BR_Q", 102, 22)
    chain((89, 22), pin_grid("L_Q", 1))
    chain(pin_grid("L_Q", 2), (89, 30))
    add_pwr("GND", 89, 30)
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    chain((71, 22), pin_grid("R2", 1))
    chain(pin_grid("R2", 2), (71, 44))
    chain((71, 44), pin_grid("L_S", 1))
    net_label("BR_S", 74, 44)

    for sref, scol in (("R3", 71), ("C_S2", 79)):
        chain((scol, 44), pin_grid(sref, 1))
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
    chain(pin_grid("L_S", 2), pin_grid("C_BLK", 1))
    chain(pin_grid("C_S", 2), (96, 44))
    net_label("BR_O", 104, 44)
    chain((103, 44), pin_grid("R_TERM", 1))
    chain(pin_grid("R_TERM", 2), (103, 52))
    add_pwr("GND", 103, 52)
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    chain(pin_grid("C_MZ", 2), (131, 15), (131, 22))

    chain(pin_grid("L_M1", 2), pin_grid("AE1", 1))
    net_label("ANT_FEED", 139, 22)
    chain((136, 22), pin_grid("C_M2", 1))
    chain(pin_grid("C_M2", 2), (136, 28))
    add_pwr("GND", 136, 28)
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    # 6. LT5538 Log Detector & Anti-Aliasing Video LPF
    # ======================================================================
    chain(pin_grid("C_BLK", 2), pin_grid("U2", 2))
    net_label("DET_IN", 118, 44)

    chain(pin_grid("U2", 3), (119, 47), pin_grid("C_INN", 1))
    net_label("DET_INN", 119, 47)
    chain(pin_grid("C_INN", 2), (119, 53))
    add_pwr("GND", 119, 53)

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    chain(pin_grid("U2", 5), (129, 38))
    add_pwr("3V3_DET", 129, 38)
    chain(pin_grid("U2", 7), (139, 42), pin_grid("C_CAPP", 1))
    net_label("CAPP", 135, 42)
    chain(pin_grid("C_CAPP", 2), (139, 38))
    chain(pin_grid("U2", 6), (145, 44), pin_grid("C_CAPM", 1))
    net_label("CAPM", 136, 44)
    chain(pin_grid("C_CAPM", 2), (145, 38))

    chain(pin_grid("U2", 4), (128, 52), (130, 52), pin_grid("U2", 9))
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    add_pwr("GND", 129, 53)

    chain(pin_grid("U2", 8), pin_grid("R_LPF", 1))
    net_label("DET_OUT", 137, 47)
    chain(pin_grid("R_LPF", 2), (157, 47))
    net_label("DET_ADC", 157, 47, just="right")
    chain((151, 47), pin_grid("TP4", 1))
    chain((151, 47), pin_grid("C_LPF", 1))
    chain(pin_grid("C_LPF", 2), (151, 53))
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    add_pwr("GND", 68, 77)

    chain(pin_grid("J2", 2), (67, 80), (76, 80), pin_grid("Q3", 3))
    net_label("VBAT_RAW", 68, 80)
    chain((76, 72), pin_grid("D_VBAT", 1))
    chain(pin_grid("D_VBAT", 2), (71, 77))
    add_pwr("GND", 71, 77)
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
    chain(pin_grid("R_BG", 2), (86, 76), (91, 76), pin_grid("Q2", 6))
    chain(pin_grid("Q2", 5), pin_grid("Q2", 6))
    net_label("VBAT_GATE", 87, 76)
    chain(pin_grid("Q2", 1), (95, 78))
    add_pwr("GND", 95, 78)

    chain(pin_grid("Q2", 2), (108, 70), pin_grid("R_BPD", 1))
    net_label("BAT_MON_EN", 101, 70)
    chain(pin_grid("R_BPD", 2), (108, 76))
    add_pwr("GND", 108, 76)

    chain(pin_grid("Q2", 3), (102, 74), pin_grid("R_B1", 1))
    net_label("VBAT_SW", 102, 74, just="right")
    chain(pin_grid("R_B1", 2), (102, 86), pin_grid("R_B2", 1))
    chain((102, 86), (109, 86), pin_grid("C_BAT", 1))
    chain((102, 86), (95, 86))
    net_label("BAT_SENSE", 95, 86)
    chain(pin_grid("R_B2", 2), (102, 92))
    add_pwr("GND", 102, 92)
    chain(pin_grid("C_BAT", 2), (109, 92))
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    add_pwr("GND", 117, 90)

    chain((123, 87), pin_grid("Q1", 3))
    net_label("DET_EN", 123, 87)
    chain((128, 87), pin_grid("R_PD", 1))
    chain(pin_grid("R_PD", 2), (128, 93))
    add_pwr("GND", 128, 93)
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

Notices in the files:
README.md:
License: Apache 2.0
Author:** Stephen K. Boachie · **License:** [Apache License 2.0](LICENSE) · **Cite via [`CITATION.cff`](CITATION.cff):
